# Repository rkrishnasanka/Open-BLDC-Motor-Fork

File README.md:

## Custom ESC Hardware

This project contains the KiCAD design files for the custom ESC PCB.
The project was designed with KiCAD Version 6.0.6 and should be able to be edited this way.

Any non standard components are located in the `Additional_Components` folder. The `bom` folder contains an HTML file generated by the iBOM plugin with the layout and placement of all components.

The `ir2130_driver` folder was a first idea for the hardware with a different driver IC which was abandoned. It is kept for documentation purposes.

The git tag `evaluation_board` contains the first produced version of this board in a bigger formfactor with additional debugging pads.

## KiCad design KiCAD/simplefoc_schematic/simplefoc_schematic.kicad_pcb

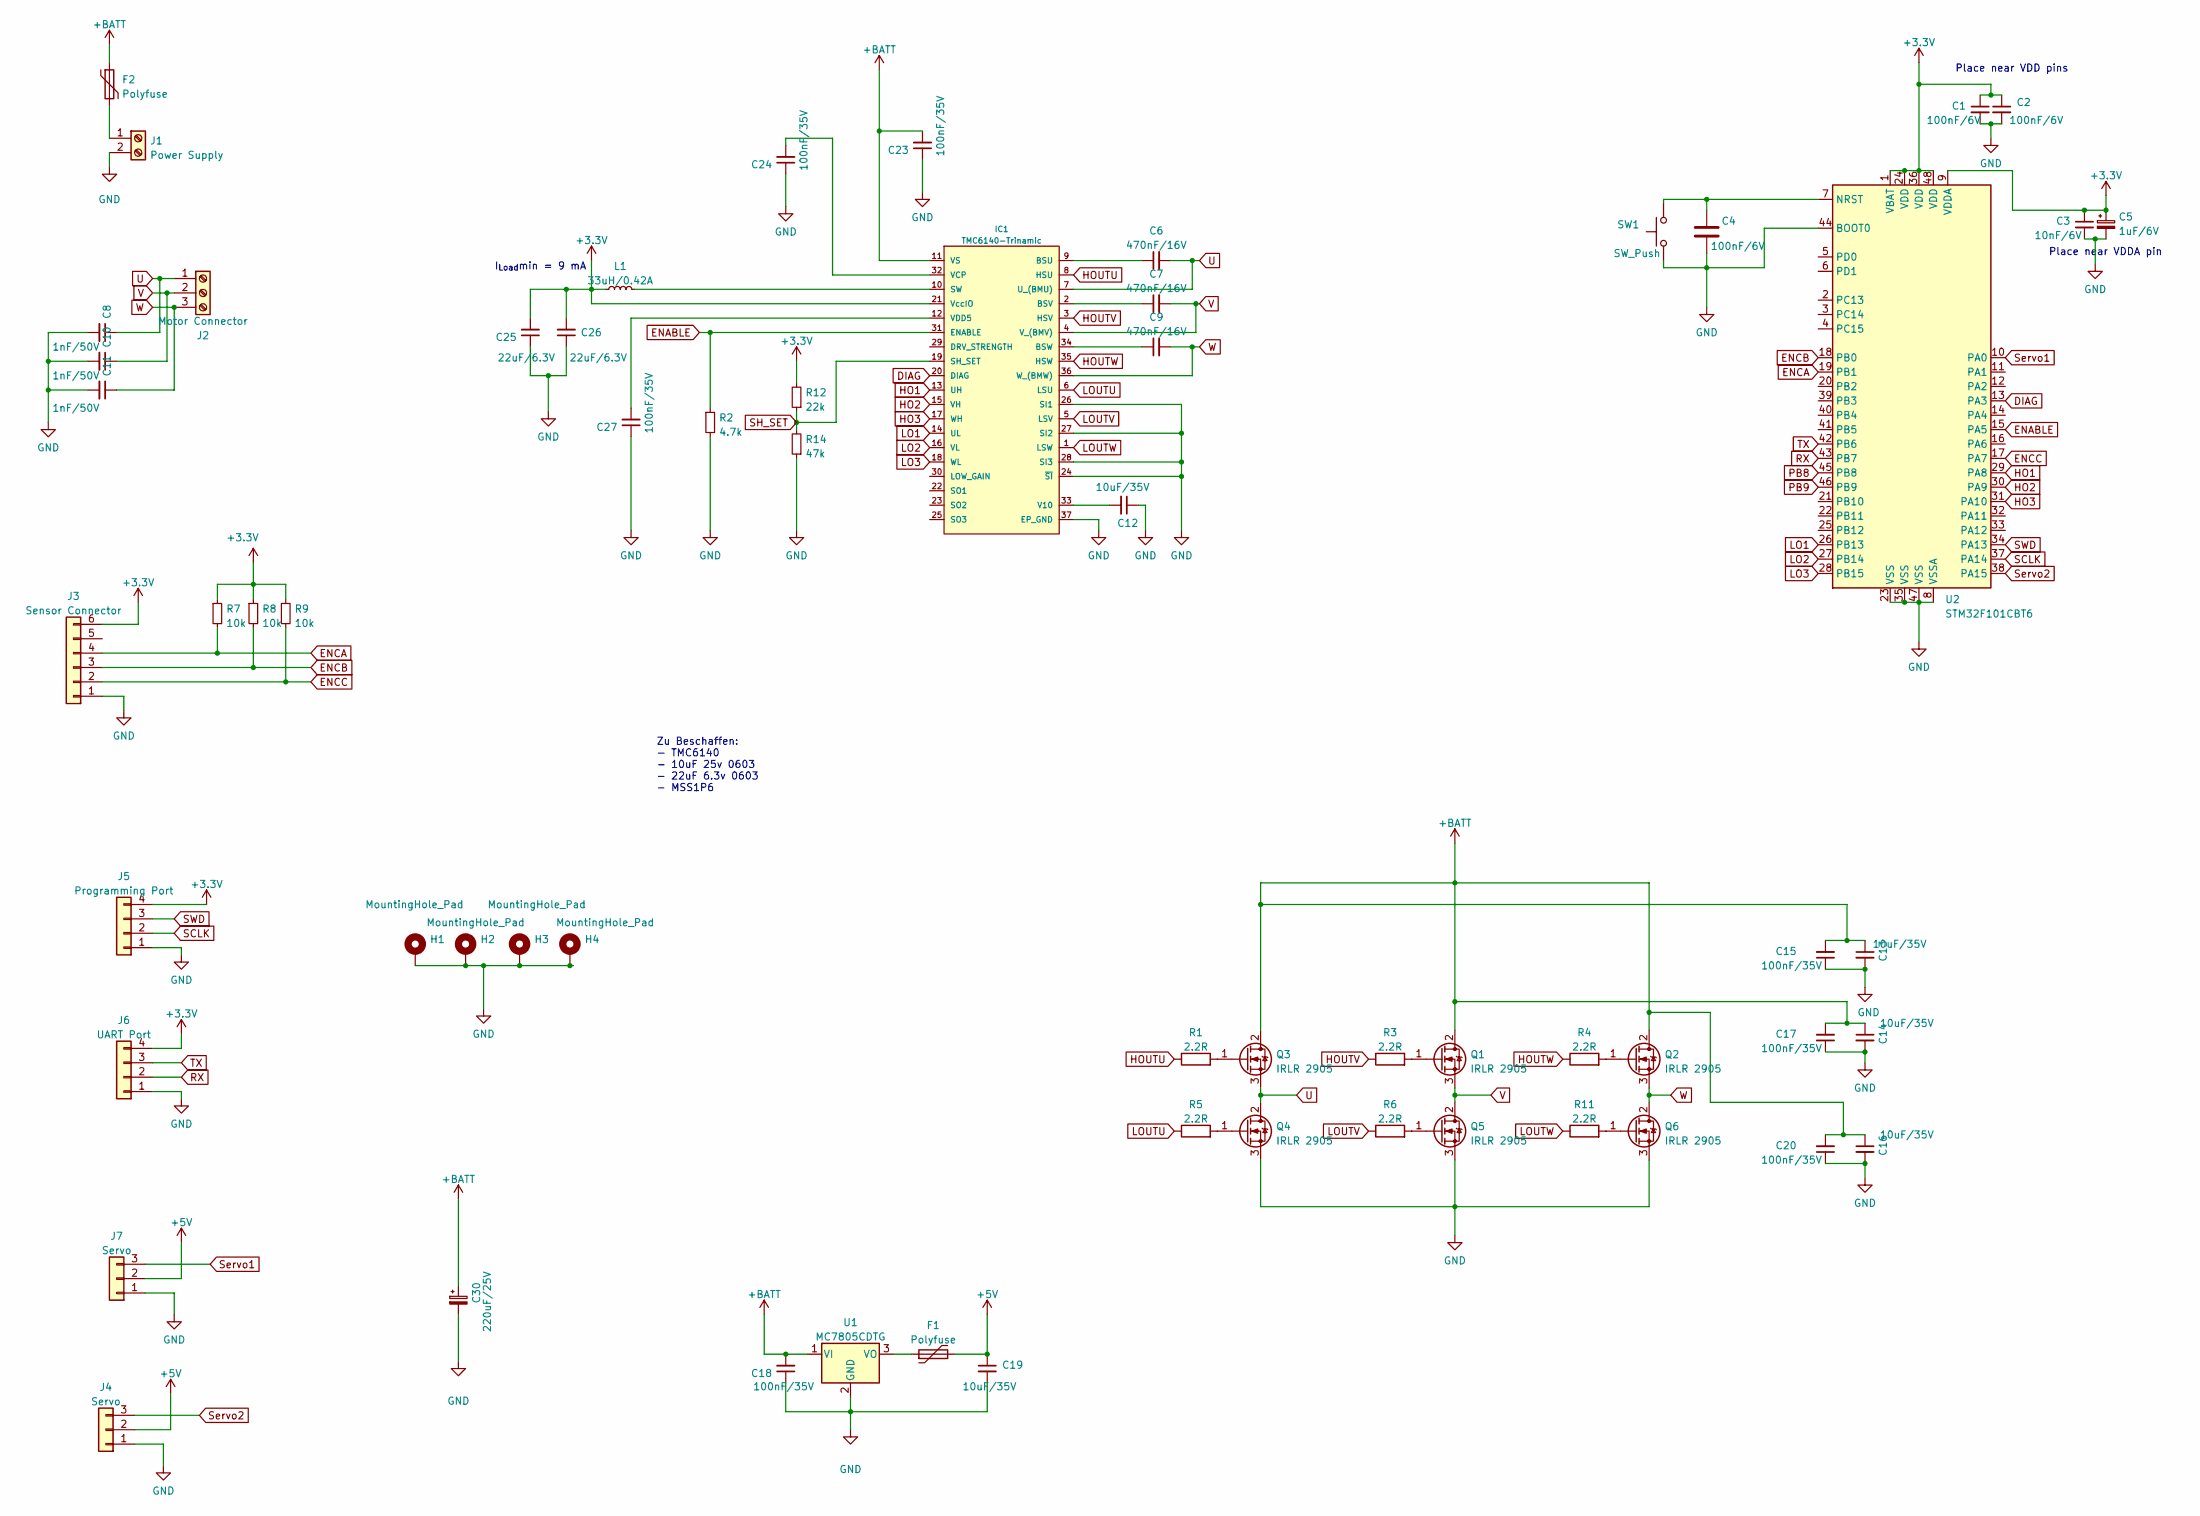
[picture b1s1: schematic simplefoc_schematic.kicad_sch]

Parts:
C1, C2, C4: 100nF/6V; C_0603_1608Metric
C3: 10nF/6V; C_0603_1608Metric
C5: 1uF/6V; C_0603_1608Metric
C6, C7, C9: 470nF/16V; C_0603_1608Metric
C8, C10, C11: 1nF/50V; C_0603_1608Metric
C12, C13, C14, C16, C19: 10uF/35V; C_0603_1608Metric
C15, C17, C18, C20, C23, C24, C27: 100nF/35V; C_0603_1608Metric
C25, C26: 22uF/6.3V; C_0603_1608Metric
C30: 220uF/25V; CP_Elec_8x10
F1: Polyfuse; Fuse_0603_1608Metric_Pad1.05x0.95mm_HandSolder
F2: Polyfuse; Fuse_2920_7451Metric_Pad2.10x5.45mm_HandSolder
H1, H2, H3, H4: MountingHole_Pad; MountingHole_2.2mm_M2_DIN965_Pad
IC1: TMC6140-Trinamic; QFN-36-1EP_5x6mm_P0.5mm_EP3.6x4.1mm
J1: Power Supply; TerminalBlock_Phoenix_MKDS-1,5-2_1x02_P5.00mm_Horizontal
J2: Motor Connector; TerminalBlock_Phoenix_MKDS-1,5-3_1x03_P5.00mm_Horizontal
J3: Sensor Connector; JST_ZH_B6B-ZR_1x06_P1.50mm_Vertical
J4, J7: Servo; PinSocket_1x03_P2.54mm_Vertical
J5: Programming Port; PinHeader_1x04_P2.54mm_Vertical
J6: UART Port; JST_XH_B4B-XH-A_1x04_P2.50mm_Vertical
L1: 33uH/0.42A; L_Fastron_1212_FPS
Q1, Q2, Q3, Q4, Q5, Q6: IRLR 2905; TO-252-2
R1, R3, R4, R5, R6, R11: 2.2R; R_0603_1608Metric
R2: 4.7k; R_0603_1608Metric
R7, R8, R9: 10k; R_0603_1608Metric
R12: 22k; R_0603_1608Metric
R14: 47k; R_0603_1608Metric
SW1: SW_Push; SW_Push_SPST_Wuerth_434121043816
U1: MC7805CDTG; TO-252-2
U2: STM32F101CBT6; LQFP-48_7x7mm_P0.5mm

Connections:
+3.3V: C1.1, C2.1, C3.1, C5.1, C25.2, C26.2, IC1.21 (VccIO), J3.6, J5.4, J6.4, L1.1, R7.1, R8.1, R9.1, R12.2, U2.1 (VBAT), U2.9 (VDDA), U2.24 (VDD), U2.36 (VDD), U2.48 (VDD)
+5V: C19.1, F1.2, J4.2, J7.2
+BATT: C13.1, C14.1, C15.2, C16.1, C17.2, C18.2, C20.2, C23.2, C30.1, F2.1, IC1.11 (VS), Q1.2 (D), Q2.2 (D), Q3.2 (D), U1.1 (VI)
DIAG: IC1.20 (DIAG), U2.13 (PA3)
ENABLE: IC1.31 (ENABLE), R2.1, U2.15 (PA5)
ENCA: J3.4, R7.2, U2.19 (PB1)
ENCB: J3.3, R8.2, U2.18 (PB0)
ENCC: J3.2, R9.2, U2.17 (PA7)
GND: C1.2, C2.2, C3.2, C4.2, C5.2, C8.2, C10.2, C11.2, C12.1, C13.2, C14.2, C15.1, C16.2, C17.1, C18.1, C19.2, C20.1, C23.1, C24.1, C25.1, C26.1, C27.1, C30.2, H1.1, H2.1, H3.1, H4.1, IC1.24 (~SI), IC1.26 (SI1), IC1.27 (SI2), IC1.28 (SI3), IC1.37 (EP_GND), J1.2, J3.1, J4.1, J5.1, J6.1, J7.1, Q4.3 (S), Q5.3 (S), Q6.3 (S), R2.2, R14.1, SW1.1, U1.2 (GND), U2.8 (VSSA), U2.23 (VSS), U2.35 (VSS), U2.44 (BOOT0), U2.47 (VSS)
HO1: IC1.13 (UH), U2.29 (PA8)
HO2: IC1.15 (VH), U2.30 (PA9)
HO3: IC1.17 (WH), U2.31 (PA10)
HOUTU: IC1.8 (HSU), R1.1
HOUTV: IC1.3 (HSV), R3.1
HOUTW: IC1.35 (HSW), R4.1
LO1: IC1.14 (UL), U2.26 (PB13)
LO2: IC1.16 (VL), U2.27 (PB14)
LO3: IC1.18 (WL), U2.28 (PB15)
LOUTU: IC1.6 (LSU), R5.1
LOUTV: IC1.5 (LSV), R6.1
LOUTW: IC1.1 (LSW), R11.1
unnamed: C4.1, SW1.2, U2.7 (NRST)
unnamed: C6.1, IC1.9 (BSU)
unnamed: C7.1, IC1.2 (BSV)
unnamed: C9.1, IC1.34 (BSW)
unnamed: C12.2, IC1.33 (V10)
unnamed: C24.2, IC1.32 (VCP)
unnamed: C27.2, IC1.12 (VDD5)
unnamed: IC1.10 (SW), L1.2
unnamed: F2.2, J1.1
unnamed: Q1.1 (G), R3.2
unnamed: Q2.1 (G), R4.2
unnamed: Q3.1 (G), R1.2
unnamed: Q4.1 (G), R5.2
unnamed: Q5.1 (G), R6.2
unnamed: Q6.1 (G), R11.2
unnamed: F1.1, U1.3 (VO)
PB8: U2.45 (PB8)
PB9: U2.46 (PB9)
RX: J6.2, U2.43 (PB7)
SCLK: J5.2, U2.37 (PA14)
SH_SET: IC1.19 (SH_SET), R12.1, R14.2
SWD: J5.3, U2.34 (PA13)
Servo1: J7.3, U2.10 (PA0)
Servo2: J4.3, U2.38 (PA15)
TX: J6.3, U2.42 (PB6)
U: C6.2, C8.1, IC1.7 (U_(BMU)), J2.1, Q3.3 (S), Q4.2 (D)
V: C7.2, C10.1, IC1.4 (V_(BMV)), J2.2, Q1.3 (S), Q5.2 (D)
W: C9.2, C11.1, IC1.36 (W_(BMW)), J2.3, Q2.3 (S), Q6.2 (D)

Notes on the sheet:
Place near VDDA pin
I_{Load}min = 9 mA
Zu Beschaffen: - TMC6140 - 10uF 25v 0603 - 22uF 6.3v 0603 - MSS1P6
Place near VDD pins

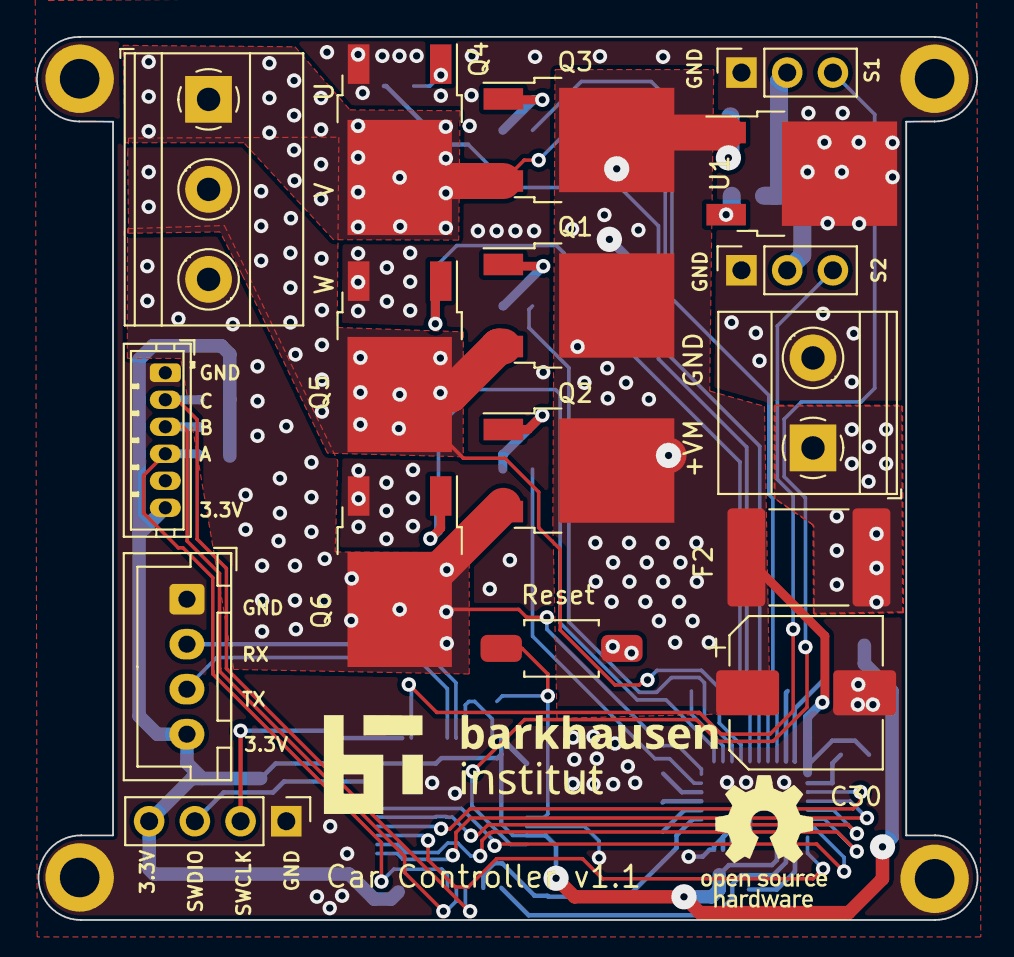
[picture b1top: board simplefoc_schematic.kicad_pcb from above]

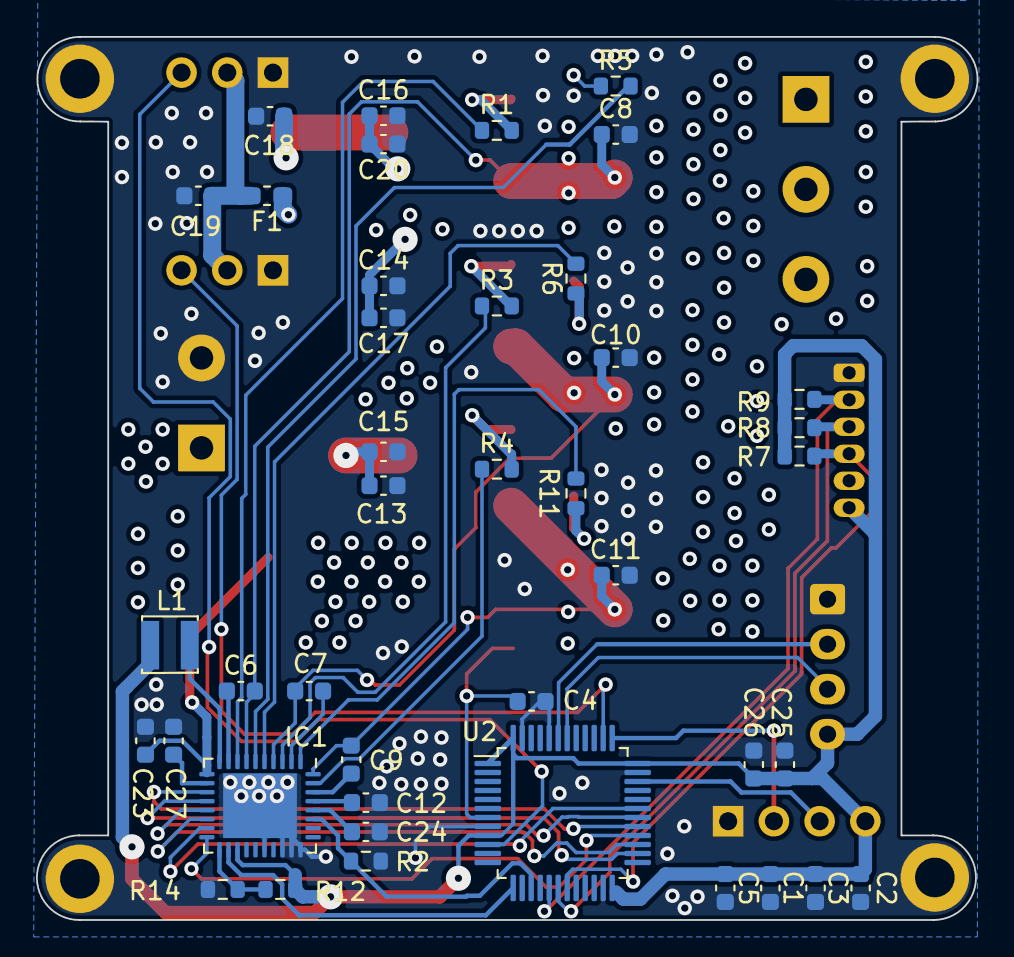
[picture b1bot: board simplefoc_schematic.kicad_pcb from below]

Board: 4 copper layers, 52.3 x 49.1 mm, 62 parts (41 on the bottom side), 47 nets.

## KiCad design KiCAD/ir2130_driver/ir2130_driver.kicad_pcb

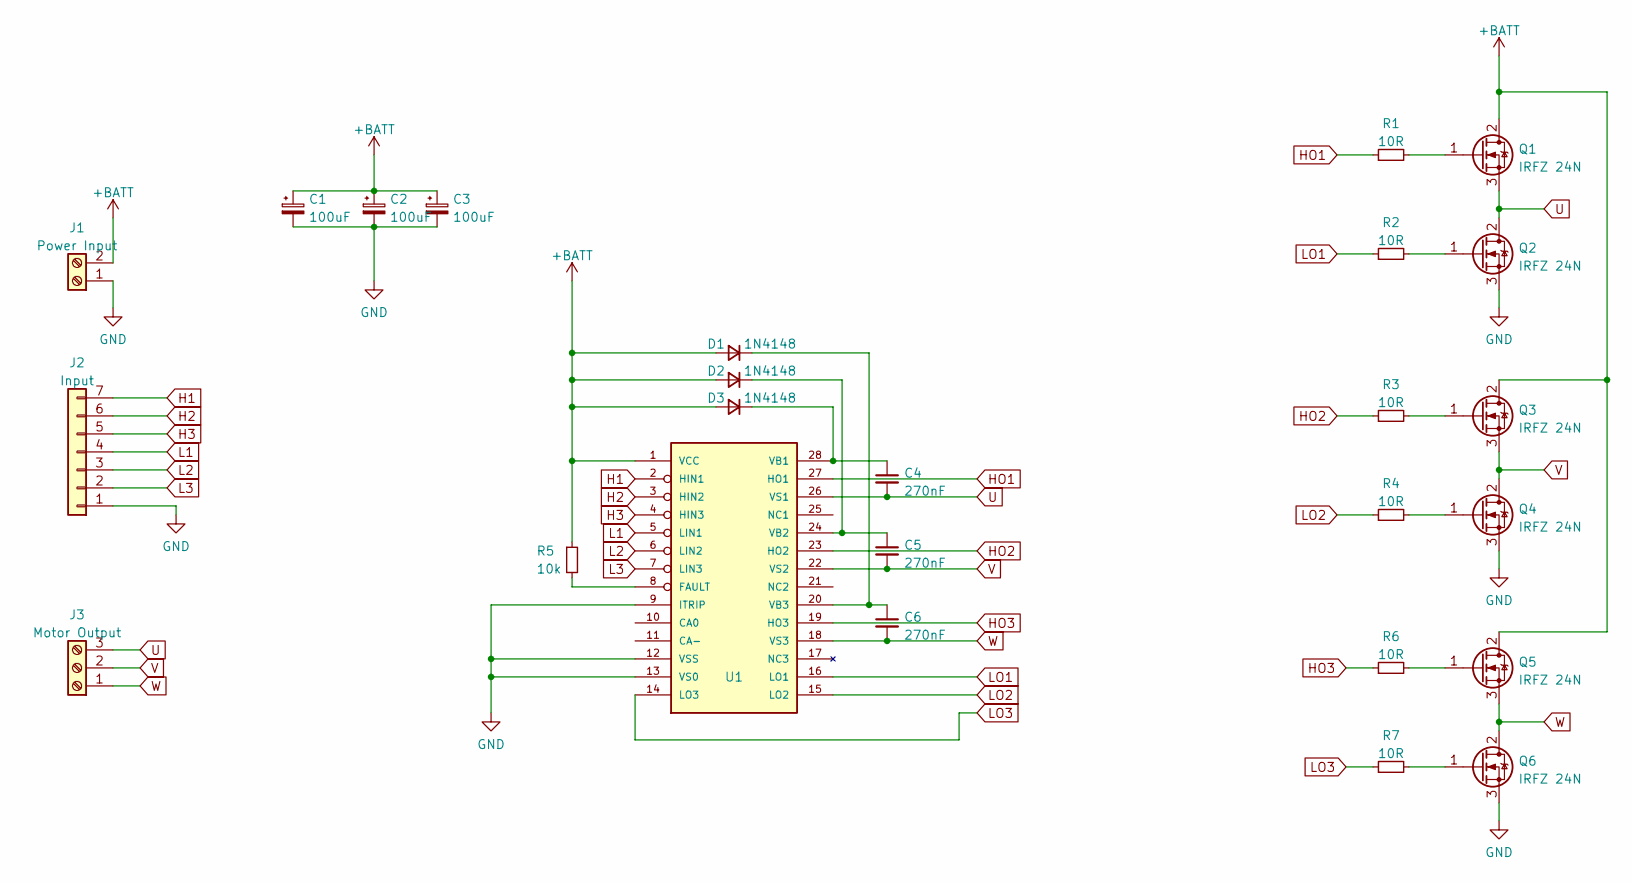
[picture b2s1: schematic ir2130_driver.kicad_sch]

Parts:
C1, C2, C3: 100uF; CP_Radial_D8.0mm_P2.50mm
C4, C5, C6: 270nF; CP_Radial_Tantal_D4.5mm_P2.50mm
D1, D2, D3: 1N4148; D_5W_P10.16mm_Horizontal
J1: Power Input; TerminalBlock_bornier-2_P5.08mm
J2: Input; PinHeader_1x07_P2.54mm_Vertical
J3: Motor Output; TerminalBlock_Altech_AK300-3_P5.00mm
Q1, Q2, Q3, Q4, Q5, Q6: IRFZ 24N; TO-220-3_Vertical
R1, R2, R3, R4, R6, R7: 10R; R_Axial_DIN0204_L3.6mm_D1.6mm_P5.08mm_Horizontal
R5: 10k; R_Axial_DIN0204_L3.6mm_D1.6mm_P5.08mm_Horizontal
U1: IR2130; DIP-28_W15.24mm_LongPads

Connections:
+BATT: C1.1, C2.1, C3.1, D1.2 (A), D2.2 (A), D3.2 (A), J1.2, Q1.2 (D), Q3.2 (D), Q5.2 (D), R5.1, U1.1 (VCC)
GND: C1.2, C2.2, C3.2, J1.1, J2.1, Q2.3 (S), Q4.3 (S), Q6.3 (S), U1.9 (ITRIP), U1.12 (VSS), U1.13 (VS0)
H1: J2.7, U1.2 (HIN1)
H2: J2.6, U1.3 (HIN2)
H3: J2.5, U1.4 (HIN3)
HO1: R1.1, U1.27 (HO1)
HO2: R3.1, U1.23 (HO2)
HO3: R6.1, U1.19 (HO3)
L1: J2.4, U1.5 (LIN1)
L2: J2.3, U1.6 (LIN2)
L3: J2.2, U1.7 (LIN3)
LO1: R2.1, U1.16 (LO1)
LO2: R4.1, U1.15 (LO2)
LO3: R7.1, U1.14 (LO3)
unnamed: C4.1, D3.1 (K), U1.28 (VB1)
unnamed: C5.1, D2.1 (K), U1.24 (VB2)
unnamed: C6.1, D1.1 (K), U1.20 (VB3)
unnamed: Q1.1 (G), R1.2
unnamed: Q2.1 (G), R2.2
unnamed: Q3.1 (G), R3.2
unnamed: Q4.1 (G), R4.2
unnamed: Q5.1 (G), R6.2
unnamed: Q6.1 (G), R7.2
unnamed: R5.2, U1.8 (FAULT)
U: C4.2, J3.3, Q1.3 (S), Q2.2 (D), U1.26 (VS1)
V: C5.2, J3.2, Q3.3 (S), Q4.2 (D), U1.22 (VS2)
W: C6.2, J3.1, Q5.3 (S), Q6.2 (D), U1.18 (VS3)

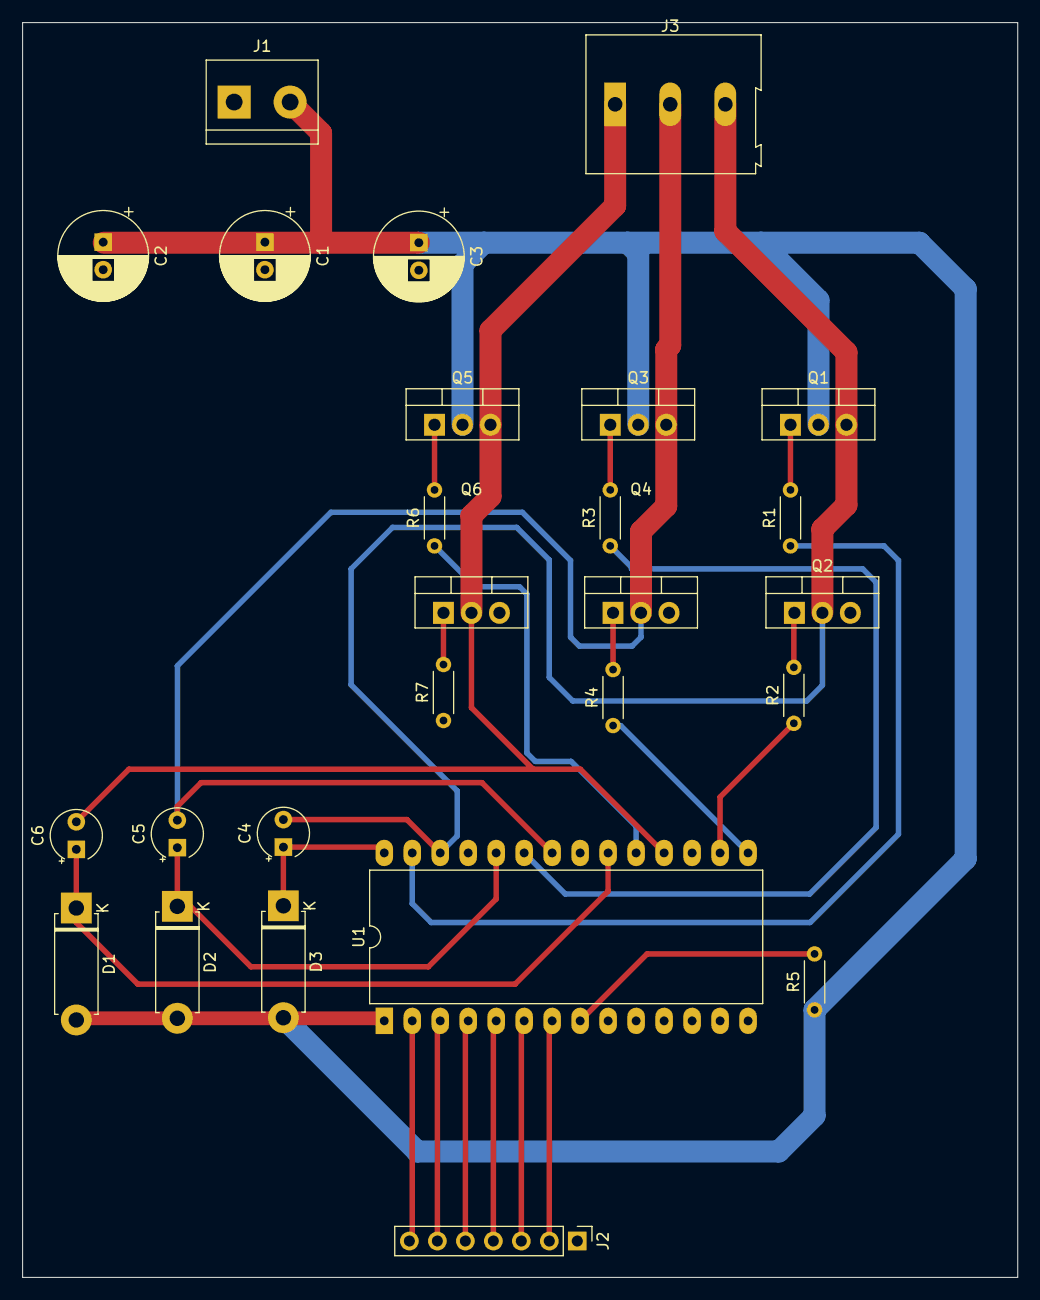
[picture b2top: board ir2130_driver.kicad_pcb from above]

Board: 2 copper layers, 90.3 x 113.9 mm, 26 parts (0 on the bottom side), 27 nets.

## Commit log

2022-08-03 Added additional project for the test board of the ir2130 driver
2022-08-03 Added PCB file for the IR2130 test board
2022-09-01 Added a standalone schematic for the STM32 part Moved from ir2130 driver to the TMC6140
2022-09-06 Finalized schematic and component selection for acquisition from distributor
2022-09-29 Removed unused components and replaced some components with smaller ones
2022-09-30 Created first board layout for test board
2022-10-04 Minor changes to power tracks
2022-11-10 First design of the final small PCB
2022-11-14 Small changes to silk screen layout
2022-11-21 Added second servo connection and fuse for servo
2022-11-21 Added polyfuse to battery input
2022-12-12 Final production version
2022-12-12 Removed the unused stm32_standalone project
2022-12-12 Added a README
2023-01-16 Change to 4 Layer PCB with better grounding
